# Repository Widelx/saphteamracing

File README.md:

### SaphTeamRacing
Course de voiture autonomes à laquelle participe l'IUT de cachan.
Année scolaire 2021/22.

Programmes MBED, Keil et Octave developpés par Guillaume de Maricourt.
Programmes d'interprétation développés par Antoine Beauvarlet.
PCB carte puissance et carte traitement développés par Axel Manadi.

Ces programmes et PCB sont réservés aux étudiants de l'IUT de Cachan uniquement.

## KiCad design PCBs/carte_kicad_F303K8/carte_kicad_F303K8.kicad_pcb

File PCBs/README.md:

# PCB - Carte DSICOF746NG

Ce dossier contient deux projets de PCBs
- Une première carte d'adaptation entre les différents modules et le microcontroleur F303K8.
- Une seconde carte (obsolète) d'adaptation entre les différents modules et la carte de contrôle DISCO F746-NG.

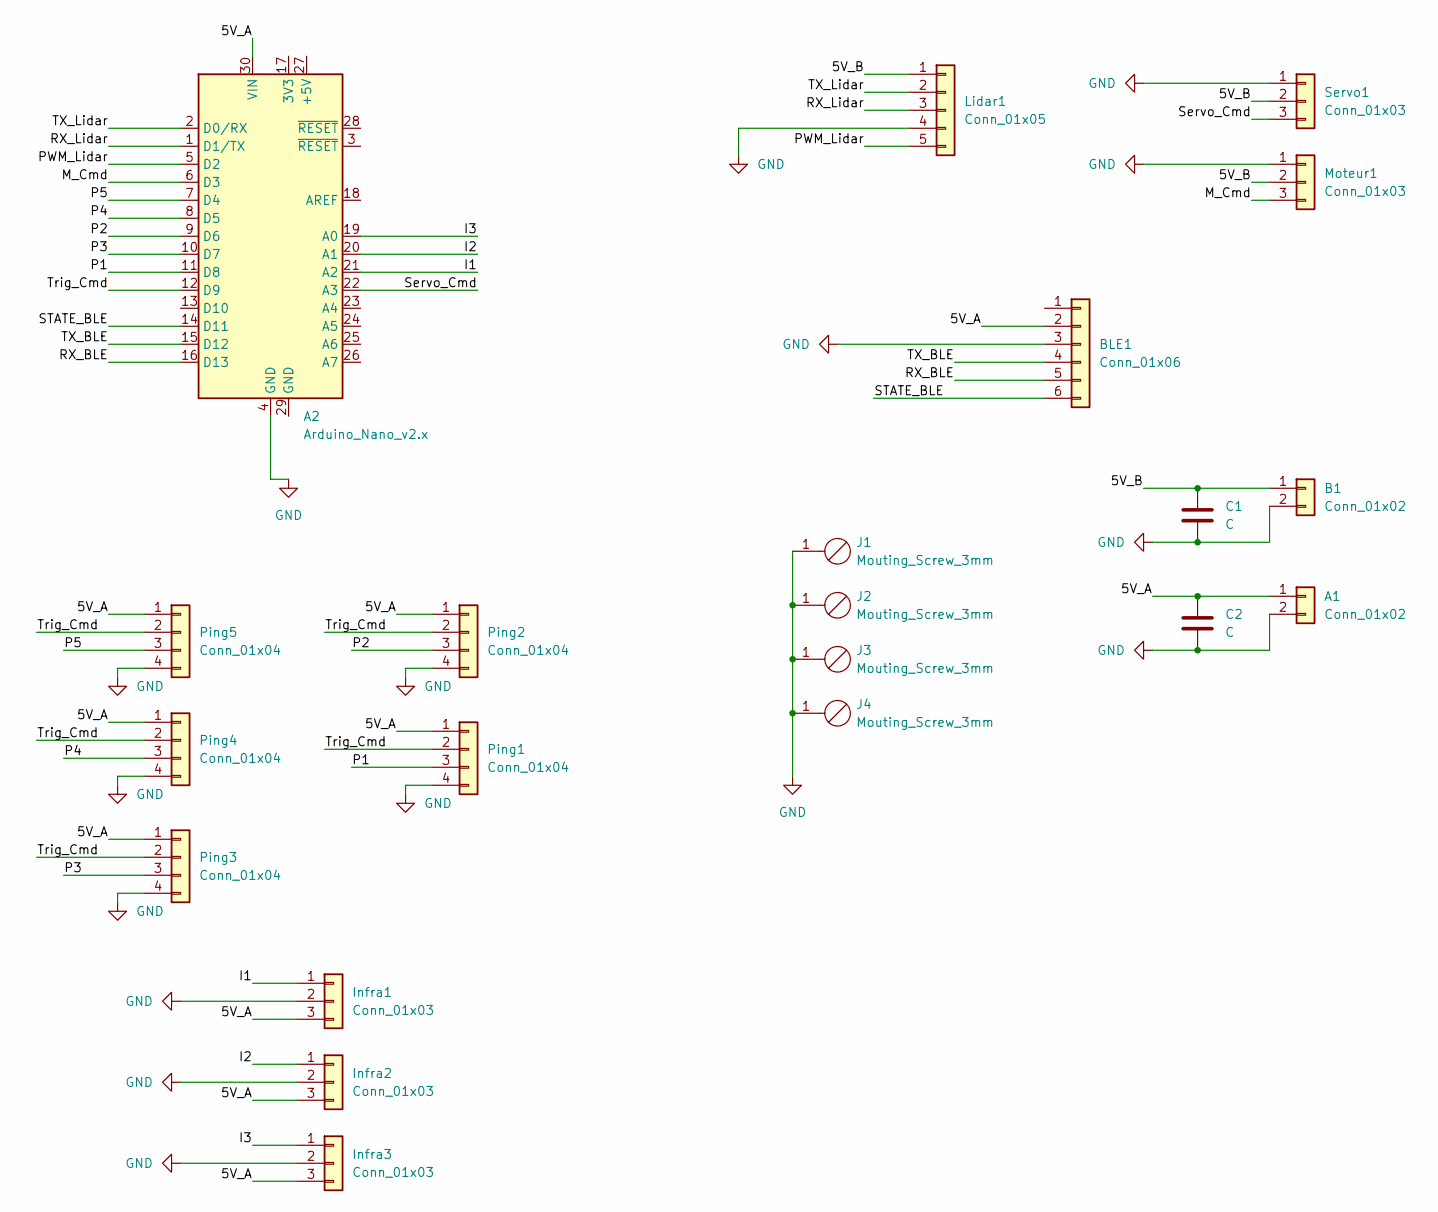
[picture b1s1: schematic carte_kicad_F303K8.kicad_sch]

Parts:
A1: Conn_01x02; PinHeader_1x02_P2.54mm_Vertical
A2: Arduino_Nano_v2.x; Arduino_Nano
B1: Conn_01x02; PinHeader_1x02_P2.54mm_Vertical
BLE1: Conn_01x06; PinHeader_1x06_P2.54mm_Vertical
C1, C2: C; C_Rect_L7.0mm_W2.5mm_P5.00mm
Infra1, Infra2, Infra3: Conn_01x03; PinHeader_1x03_P2.54mm_Vertical
J1, J2, J3, J4: Mouting_Screw_3mm
Lidar1: Conn_01x05; PinHeader_1x05_P2.54mm_Vertical
Moteur1: Conn_01x03; PinHeader_1x03_P2.54mm_Vertical
Ping1, Ping2, Ping3, Ping4, Ping5: Conn_01x04; PinHeader_1x04_P2.54mm_Vertical
Servo1: Conn_01x03; PinHeader_1x03_P2.54mm_Vertical

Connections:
/5V_A: A1.1, A2.30 (VIN), BLE1.2, C2.1, Infra1.3, Infra2.3, Infra3.3, Ping1.1, Ping2.1, Ping3.1, Ping4.1, Ping5.1
/5V_B: B1.1, C1.1, Lidar1.1, Moteur1.2, Servo1.2
/I1: A2.21 (A2), Infra1.1
/I2: A2.20 (A1), Infra2.1
/I3: A2.19 (A0), Infra3.1
/M_Cmd: A2.6 (D3), Moteur1.3
/P1: A2.11 (D8), Ping1.3
/P2: A2.9 (D6), Ping2.3
/P3: A2.10 (D7), Ping3.3
/P4: A2.8 (D5), Ping4.3
/P5: A2.7 (D4), Ping5.3
/PWM_Lidar: A2.5 (D2), Lidar1.5
/RX_BLE: A2.16 (D13), BLE1.5
/RX_Lidar: A2.1 (D1/TX), Lidar1.3
/STATE_BLE: A2.14 (D11), BLE1.6
/Servo_Cmd: A2.22 (A3), Servo1.3
/TX_BLE: A2.15 (D12), BLE1.4
/TX_Lidar: A2.2 (D0/RX), Lidar1.2
/Trig_Cmd: A2.12 (D9), Ping1.2, Ping2.2, Ping3.2, Ping4.2, Ping5.2
GND: A1.2, A2.4 (GND), B1.2, BLE1.3, C1.2, C2.2, Infra1.2, Infra2.2, Infra3.2, J1.1, J2.1, J3.1, J4.1, Lidar1.4, Moteur1.1, Ping1.4, Ping2.4, Ping3.4, Ping4.4, Ping5.4, Servo1.1

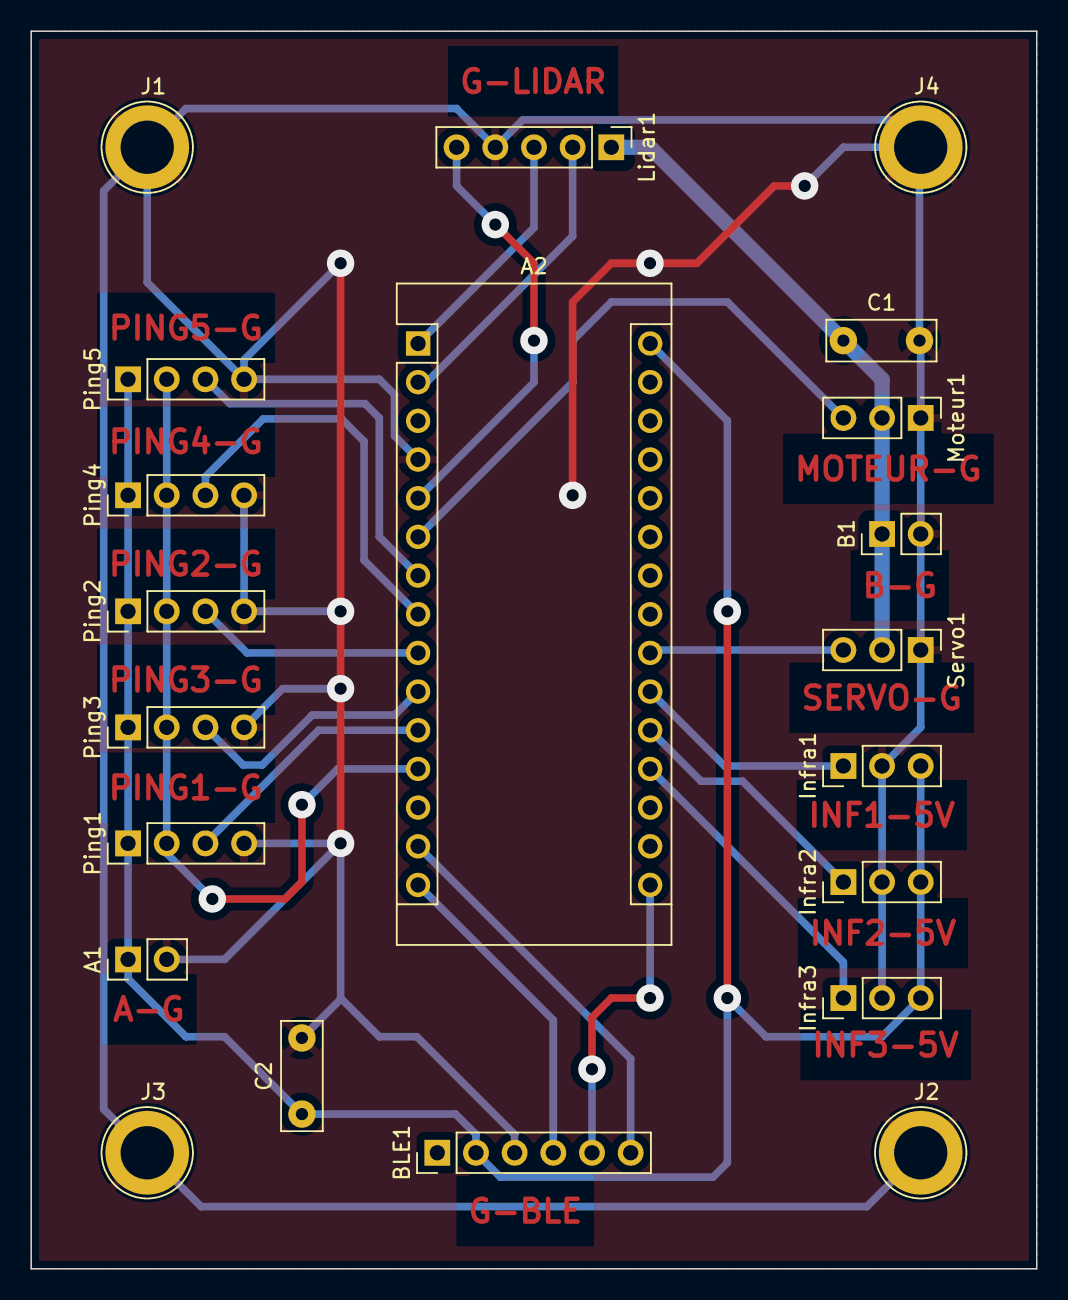
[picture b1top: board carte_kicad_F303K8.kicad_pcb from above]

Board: 2 copper layers, 66.0 x 81.3 mm, 21 parts (0 on the bottom side), 20 nets.

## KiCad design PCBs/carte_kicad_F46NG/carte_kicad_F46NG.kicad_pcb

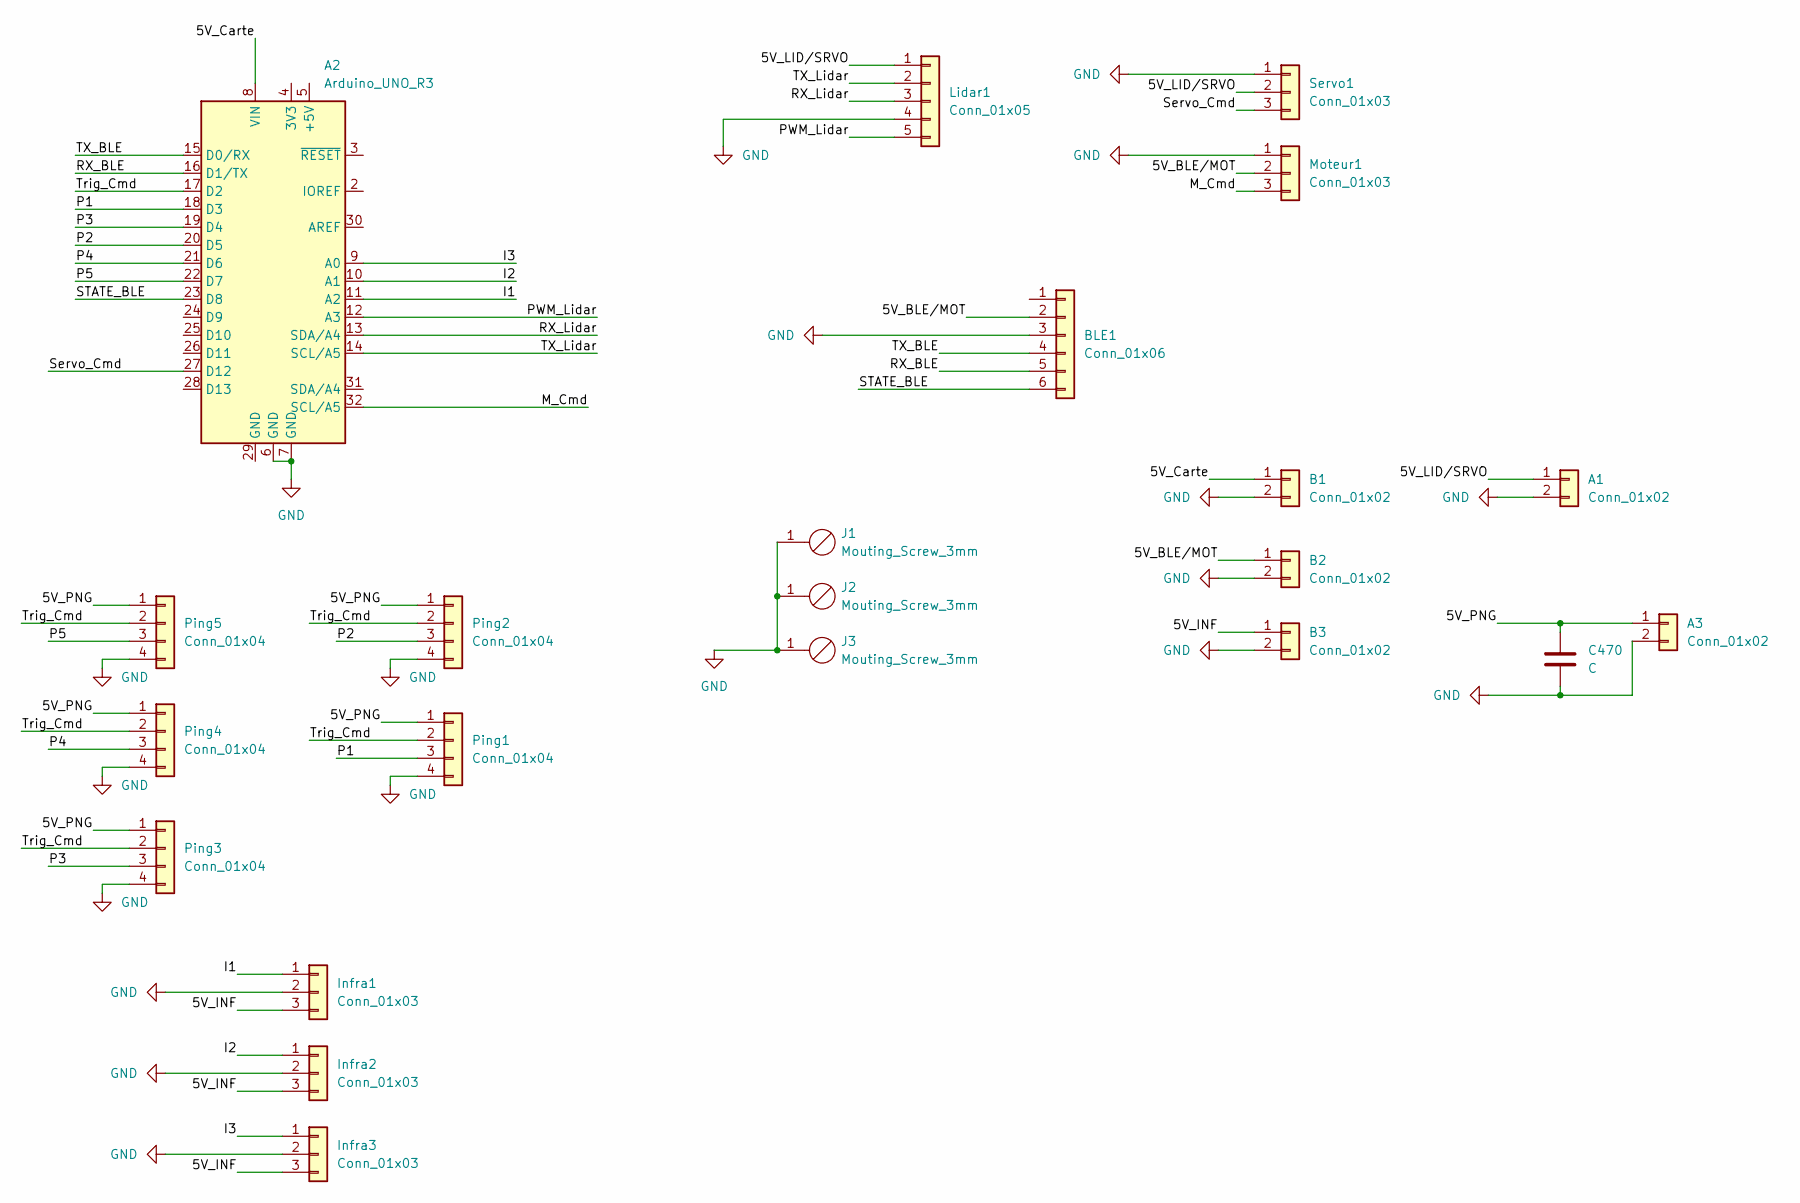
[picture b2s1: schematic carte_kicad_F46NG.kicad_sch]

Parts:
A1, A3: Conn_01x02; PinHeader_1x02_P2.54mm_Vertical
A2: Arduino_UNO_R3
B1, B2, B3: Conn_01x02; PinHeader_1x02_P2.54mm_Vertical
BLE1: Conn_01x06; PinHeader_1x06_P2.54mm_Vertical
C470: C; C_Rect_L7.0mm_W2.5mm_P5.00mm
Infra1, Infra2, Infra3: Conn_01x03; PinHeader_1x03_P2.54mm_Vertical
J1, J2, J3: Mouting_Screw_3mm
Lidar1: Conn_01x05; PinHeader_1x05_P2.54mm_Vertical
Moteur1: Conn_01x03; PinHeader_1x03_P2.54mm_Vertical
Ping1, Ping2, Ping3, Ping4, Ping5: Conn_01x04; PinHeader_1x04_P2.54mm_Vertical
Servo1: Conn_01x03; PinHeader_1x03_P2.54mm_Vertical

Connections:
/5V_BLE/MOT: B2.1, BLE1.2, Moteur1.2
/5V_Carte: A2.8 (VIN), B1.1
/5V_INF: B3.1, Infra1.3, Infra2.3, Infra3.3; also elsewhere on the board
/5V_LID/SRVO: A1.1, Lidar1.1, Servo1.2
/5V_PNG: A3.1, C470.1, Ping1.1, Ping2.1, Ping3.1, Ping4.1, Ping5.1
/I1: A2.11 (A2), Infra1.1
/I2: A2.10 (A1), Infra2.1
/I3: A2.9 (A0), Infra3.1; also elsewhere on the board
/M_Cmd: A2.32 (SCL/A5), Moteur1.3
/P1: A2.18 (D3), Ping1.3
/P2: A2.20 (D5), Ping2.3
/P3: A2.19 (D4), Ping3.3
/P4: A2.21 (D6), Ping4.3
/P5: A2.22 (D7), Ping5.3
/PWM_Lidar: A2.12 (A3), Lidar1.5
/RX_BLE: A2.16 (D1/TX), BLE1.5
/RX_Lidar: A2.13 (SDA/A4), Lidar1.3
/STATE_BLE: A2.23 (D8), BLE1.6
/Servo_Cmd: A2.27 (D12), Servo1.3
/TX_BLE: A2.15 (D0/RX), BLE1.4
/TX_Lidar: A2.14 (SCL/A5), Lidar1.2
/Trig_Cmd: A2.17 (D2), Ping1.2, Ping2.2, Ping3.2, Ping4.2, Ping5.2
GND: A1.2, A2.6 (GND), A2.7 (GND), A3.2, B1.2, B2.2, B3.2, BLE1.3, C470.2, Infra1.2, Infra2.2, Infra3.2, J1.1, J2.1, J3.1, Lidar1.4, Moteur1.1, Ping1.4, Ping2.4, Ping3.4, Ping4.4, Ping5.4, Servo1.1; also elsewhere on the board

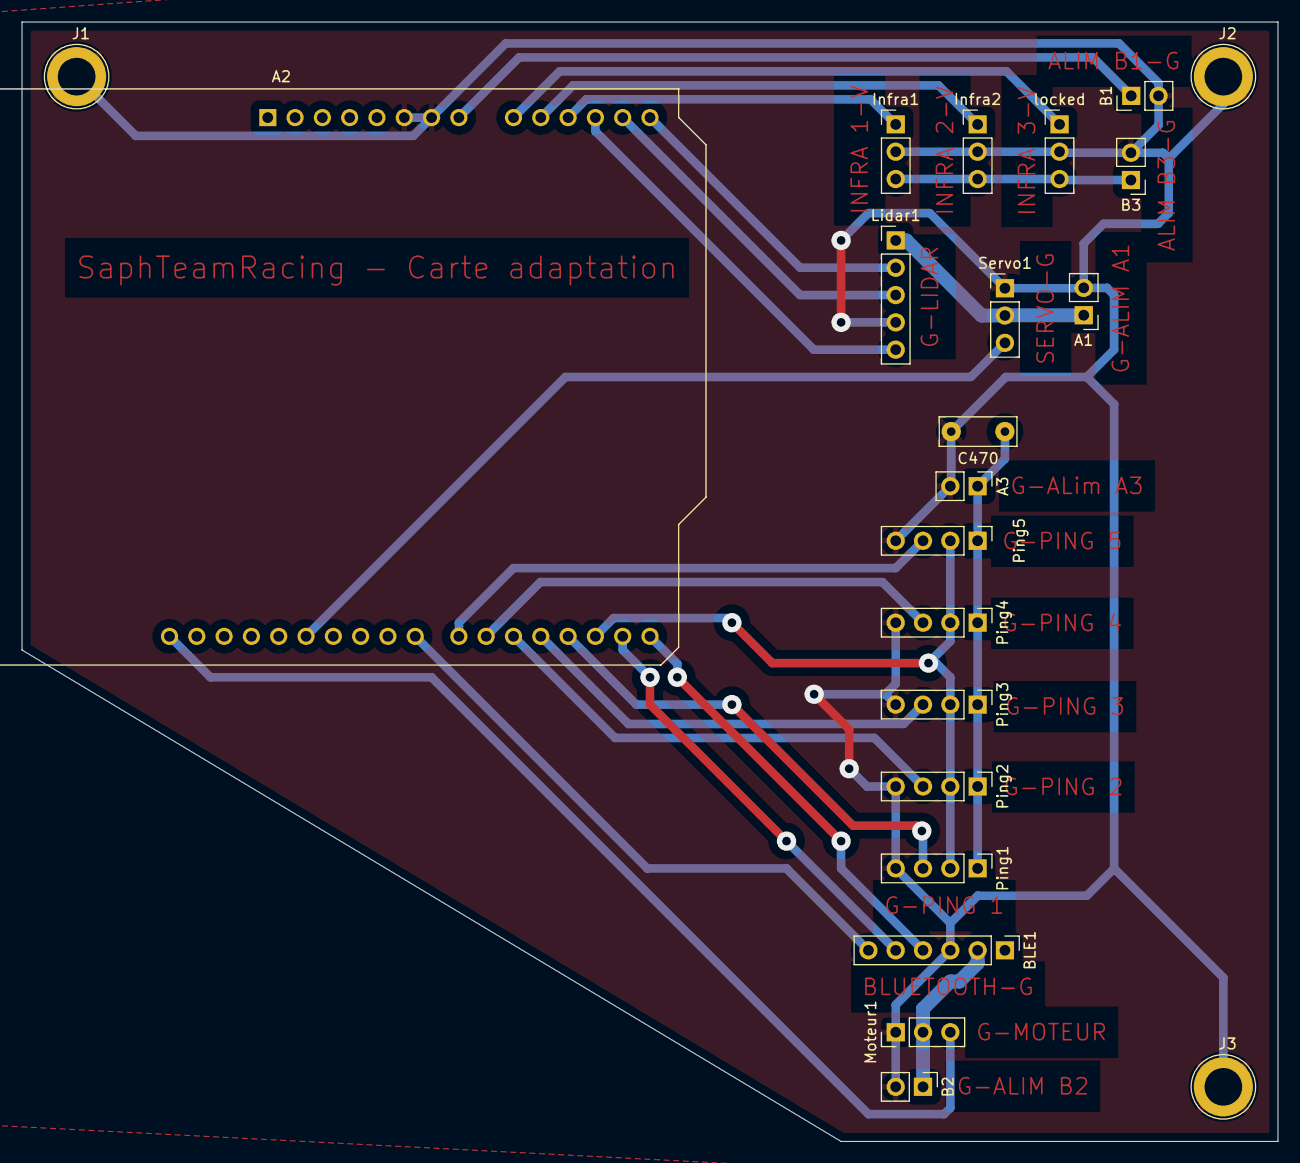
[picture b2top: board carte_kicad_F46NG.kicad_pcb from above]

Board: 2 copper layers, 116.8 x 104.1 mm, 22 parts (0 on the bottom side), 23 nets.

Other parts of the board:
locked: Conn_01x03; PinHeader_1x03_P2.54mm_Vertical

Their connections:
/5V_INF: locked.3; also elsewhere on the board
/I3: locked.1; also elsewhere on the board
GND: locked.2; also elsewhere on the board

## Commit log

2021-11-18 Ajoute les premiers fichiers de la carte KEIL
2021-12-05 ajoute la librairie Lidar
2021-12-05 Ajoute les instructions de la librairie
2021-12-05 Ajout d'instructions et MAJ
2021-12-05 Ajoute l'application de visualisation du LiDAR
2021-12-05 Ajout et MAJ
2021-12-05 Ajout d'un README
2021-12-05 Perfectionne l'application de visualisation du LiDAR
2021-12-05 MAJ des instructions + complétion
2021-12-05 Actualise les librairies et introduit Car.h/Car.cpp
2021-12-09 Refonte bibliothèques, séparation de Lidar et BLE
2021-12-09 Update des directives
    Directives MAJ après l'ajout de bluetooth.h et bluetooth.c
2021-12-09 Séparation des scripts (refonte)
2021-12-10 Les angless sont ajustés
2021-12-28 Optimisation de la libaririe et corrections mineures
2021-12-31 Améliore les performances
2022-01-02 Améliore les performances et résout des incohérences
2022-01-07 Corrige des erreurs
2022-01-15 Mise en forme pour le rapport de fin de semestre 3
2022-01-16 Résout une incohérence
2022-01-24 Ajoute le rapport
2022-01-24 Ajoute datasheet infrarouge
2022-01-24 Modifie dossier lidar
2022-01-26 Met à jour des datasheets
2022-01-26 Ajoute le PCB kicad DISCO F746 NG
2022-01-26 Met à jour le PCB kicad DISCO F746 NG
2022-01-26 Met à jour le README
2022-01-26 Ajoute un fichier README
2022-01-26 Met à jout les fichiers
2022-01-27 MAJ le PCB
2022-01-27 Ajout des modèles 3D
2022-01-27 Ajoute une PINMAP en accord avec le PCB et met a jour les libairies
2022-02-04 Ajout du PCB pour F303K8
2022-02-04 Ajoute la PINMAPF303K8
2022-02-07 MAJ rapport
2022-02-07 Modifie la documentation
2022-02-07 Ajoute images
2022-02-07 Modifie les images
2022-02-24 Correction des bugs majeurs, version stable
